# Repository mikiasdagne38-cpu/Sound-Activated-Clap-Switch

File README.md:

# Sound-Activated-Clap-Switch
This circuit listens for a loud noise (like a hand clap) and switches a high-power device ON or OFF every time you clap. It uses a microphone to hear, an amplifier to boost the sound, and a relay to safely switch heavy power.

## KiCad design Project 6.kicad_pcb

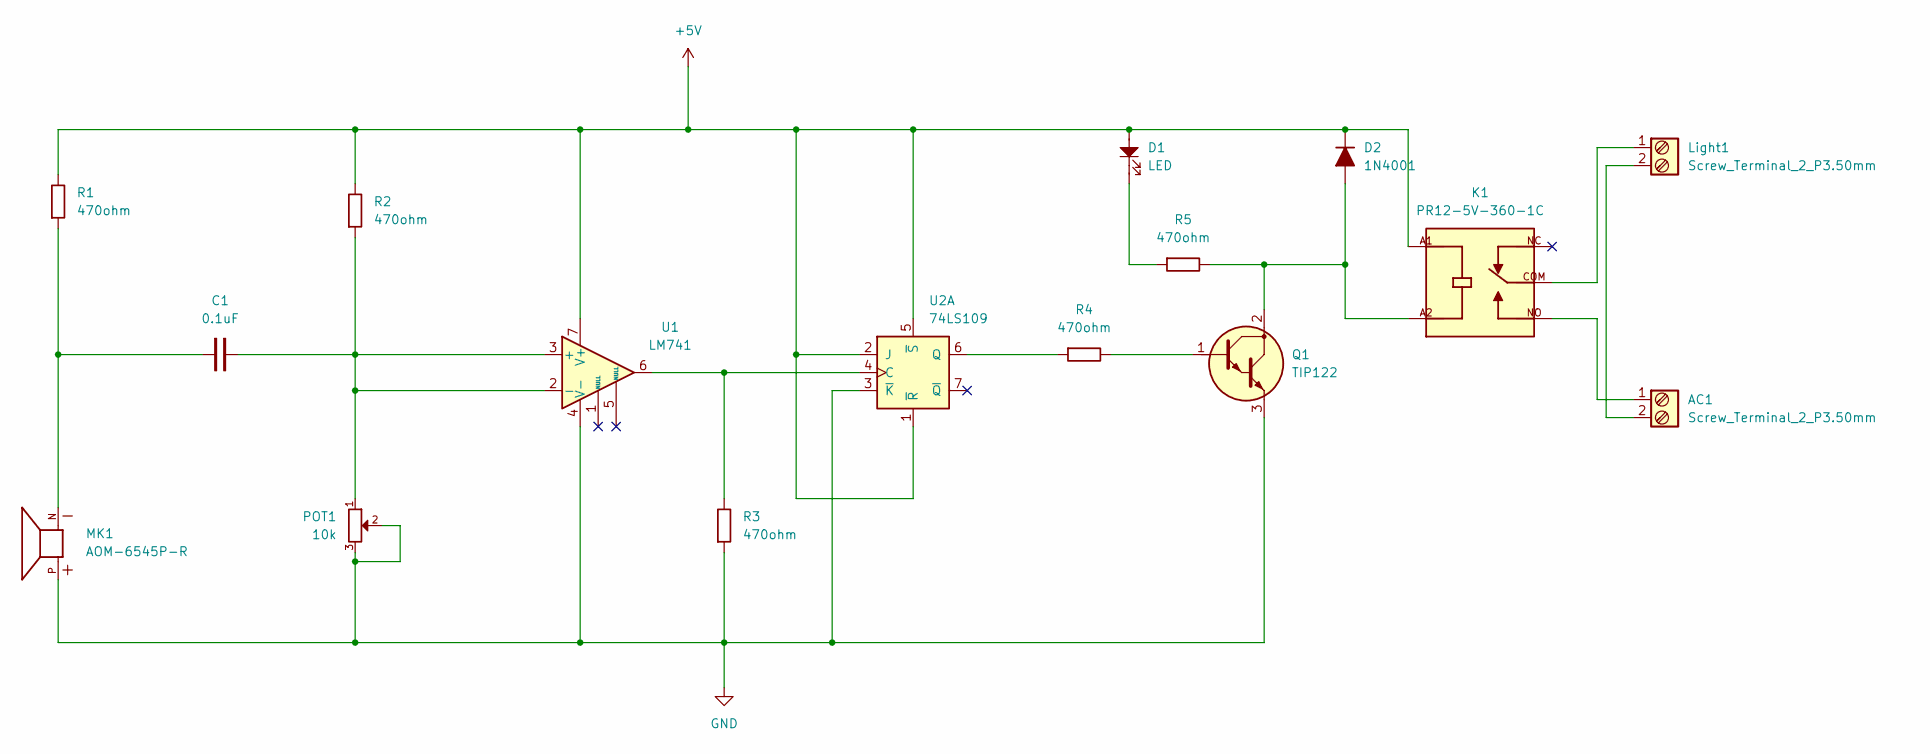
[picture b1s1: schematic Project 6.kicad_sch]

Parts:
AC1: Screw_Terminal_2_P3.50mm; TerminalBlock_Phoenix_PT-1,5-2-3.5-H_1x02_P3.50mm_Horizontal
C1: 0.1uF; C_Disc_D3.0mm_W2.0mm_P2.50mm
D1: LED; LED_D5.0mm
D2: 1N4001; D_DO-41_SOD81_P7.62mm_Horizontal
K1: PR12-5V-360-1C; RELAY_PR12-5V-360-1C; PARTREV 1.0
Light1: Screw_Terminal_2_P3.50mm; TerminalBlock_Phoenix_PT-1,5-2-3.5-H_1x02_P3.50mm_Horizontal
MK1: AOM-6545P-R; MIC_AOM-6545P-R; PARTREV D
POT1: 10k; TRIM_3296W-1-250
Q1: TIP122; TO-220-3_Vertical_BCE
R1, R2, R3, R4, R5: 470ohm; R_Axial_DIN0207_L6.3mm_D2.5mm_P10.16mm_Horizontal
U1: LM741; DIP-8_W7.62mm
U2: 74LS109; DIP794W45P254L959H508Q8

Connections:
+5V: D1.2, D2.1 (K), K1.A1, R1.2, R2.2, U1.7 (V+), U2.1 (~R), U2.2 (J), U2.5 (~S)
GND: MK1.P, POT1.2, POT1.3, Q1.3 (E), R3.1, U1.4 (V-), U2.3 (~K)
unnamed: AC1.1, K1.NO
unnamed: AC1.2, Light1.2
unnamed: C1.1, MK1.N, R1.1
unnamed: D1.1, R5.1
unnamed: D2.2 (A), K1.A2, Q1.2 (C), R5.2
unnamed: K1.COM, Light1.1
unnamed: Q1.1 (B), R4.2
unnamed: C1.2, POT1.1, R2.1, U1.2 (-), U1.3 (+)
unnamed: R3.2, U1.6, U2.4 (C)
unnamed: R4.1, U2.6 (Q)

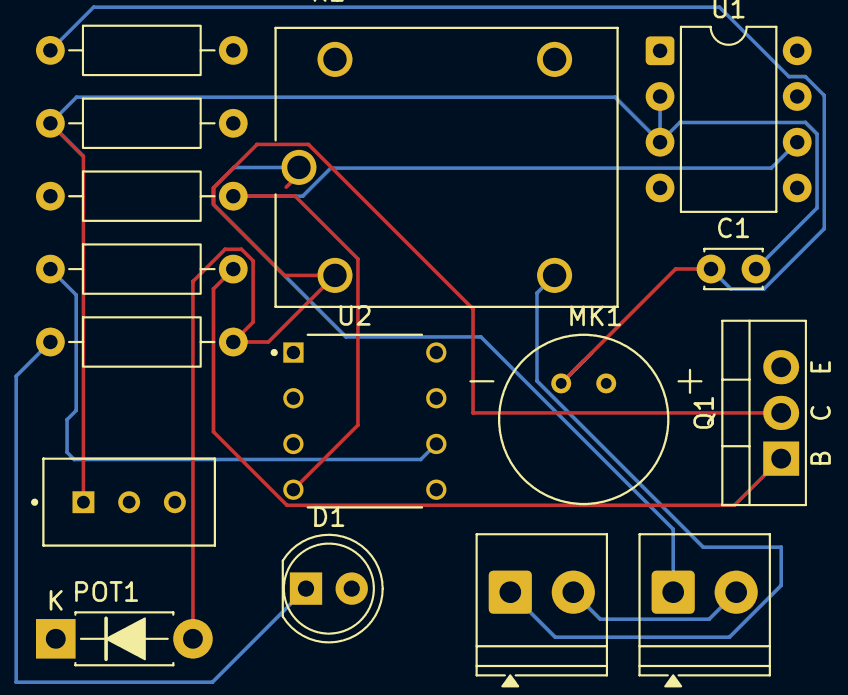
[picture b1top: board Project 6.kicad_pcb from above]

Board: 4 copper layers, 16 parts (0 on the bottom side), 12 nets.
